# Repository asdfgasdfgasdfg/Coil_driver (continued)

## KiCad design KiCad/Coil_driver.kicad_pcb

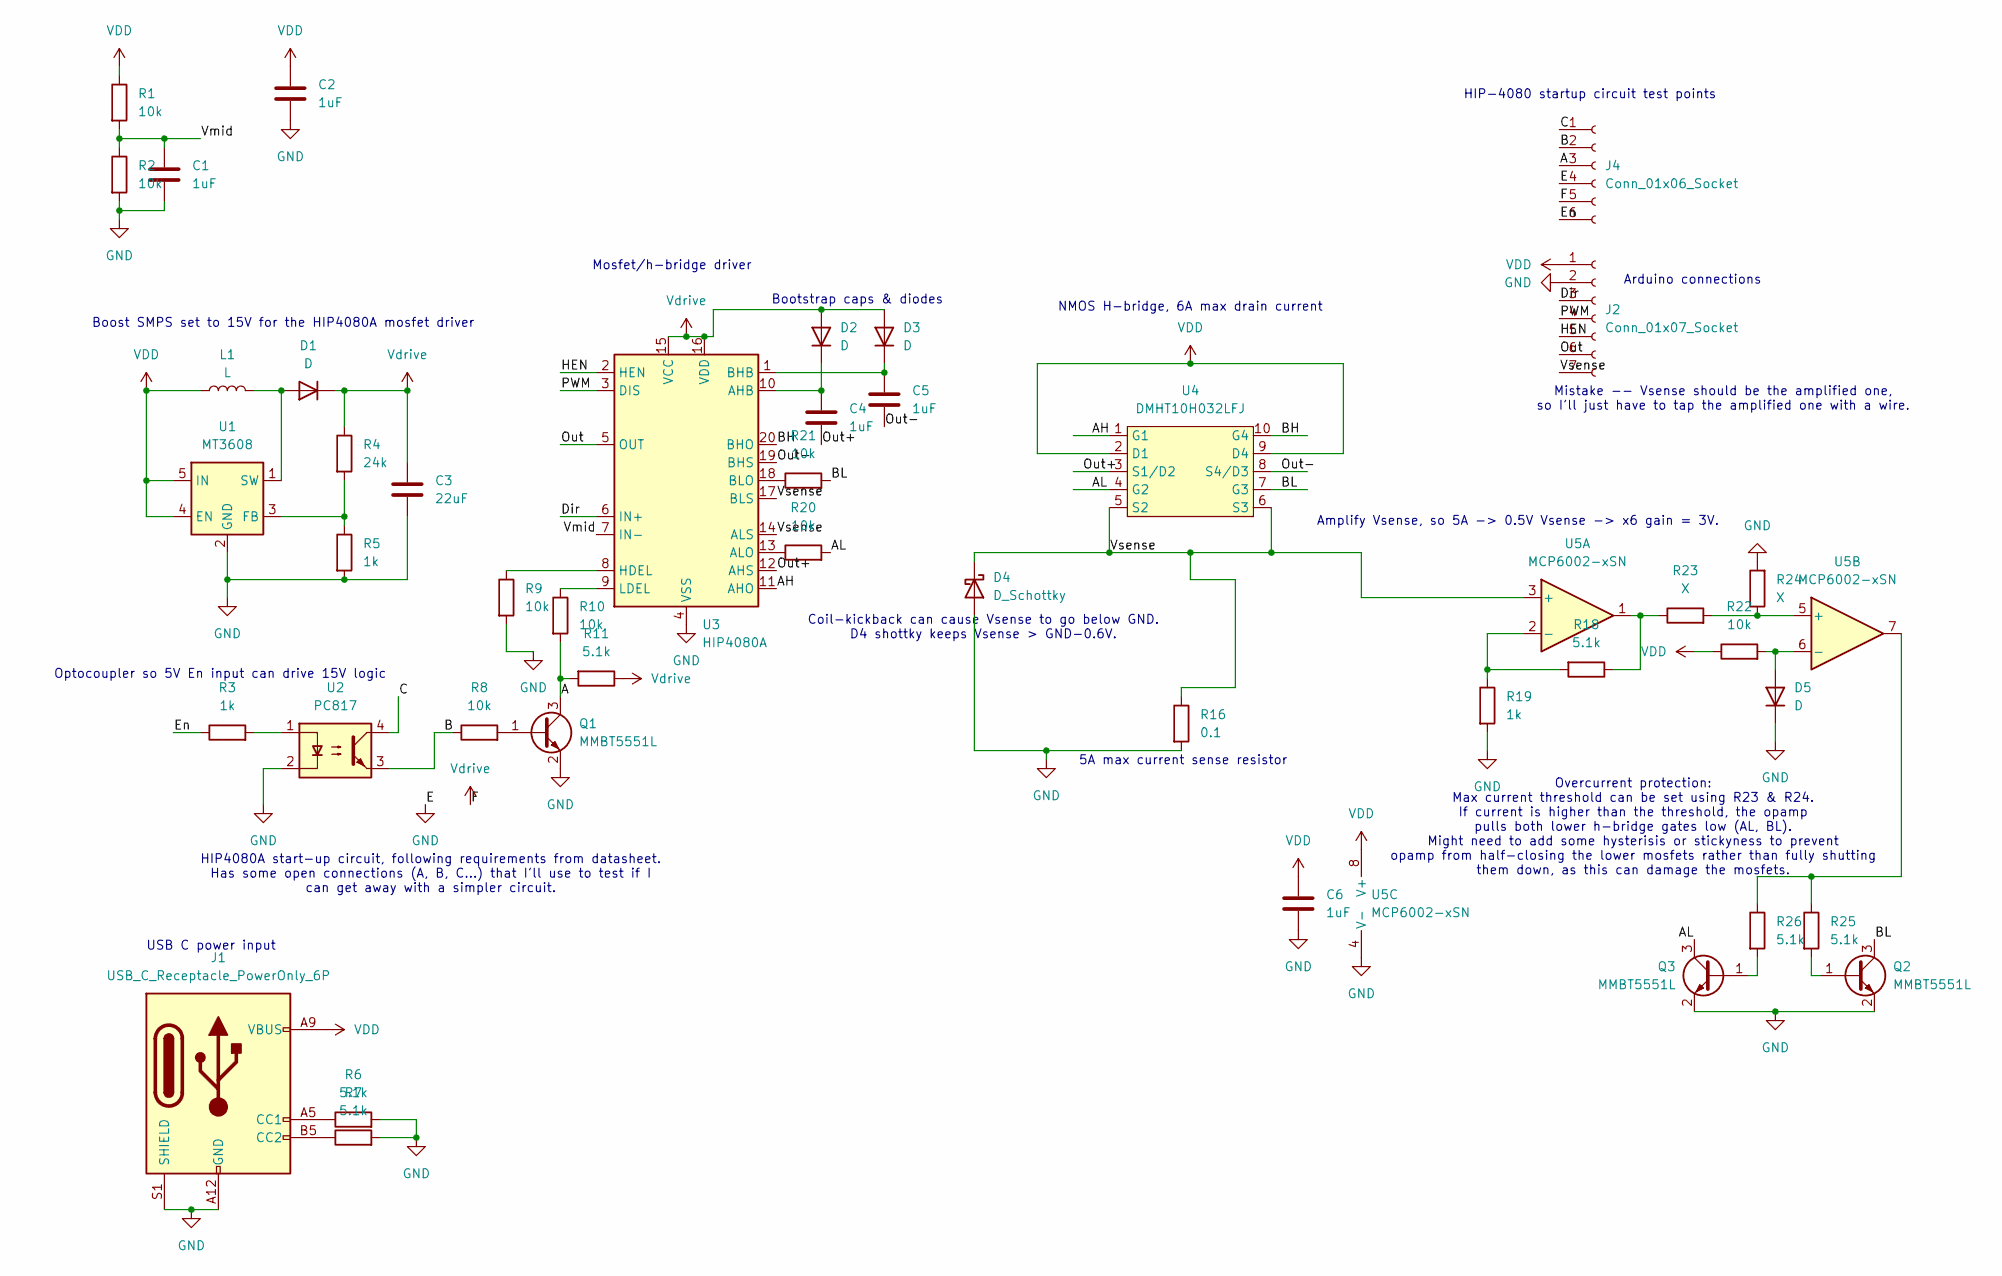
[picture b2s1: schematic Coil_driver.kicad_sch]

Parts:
C1, C2, C4, C5, C6: 1uF; C_0603_1608Metric
C3: 22uF; C_1206_3216Metric
D1, D2, D3, D5: D; D_SOD-123
D4: D_Schottky; D_SMA
J1: USB_C_Receptacle_PowerOnly_6P; USB_C_Receptacle_GCT_USB4135-GF-A_6P_TopMnt_Horizontal; LCSC C2927028
J2: Conn_01x07_Socket; PinSocket_1x07_P2.54mm_Vertical
J4: Conn_01x06_Socket; PinSocket_1x06_P2.54mm_Vertical
L1: L; L_Axial_L5.3mm_D2.2mm_P2.54mm_Vertical_Vishay_IM-1
Q1, Q2, Q3: MMBT5551L; SOT-23
R1, R2, R8, R9, R10, R20, R21, R22: 10k; R_0603_1608Metric
R3, R5, R19: 1k; R_0603_1608Metric
R4: 24k; R_0603_1608Metric
R6, R7: 5.1k; R_0603_1608Metric; LCSC C23186
R11, R18, R25, R26: 5.1k; R_0603_1608Metric
R16: 0.1; R_1206_3216Metric
R23, R24: X; R_Axial_DIN0204_L3.6mm_D1.6mm_P1.90mm_Vertical
U1: MT3608; SOT-23-6
U2: PC817; DIP-4_W7.62mm
U3: HIP4080A; SOIC-20W_7.5x12.8mm_P1.27mm
U4: DMHT10H032LFJ; V-DFN5045-12
U5: MCP6002-xSN; SOIC-8_3.9x4.9mm_P1.27mm

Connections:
/A: J4.3, Q1.3 (C), R10.2, R11.2
/AH: U3.11 (AHO), U4.1 (G1)
/AL: Q3.3 (C), R20.2, U4.4 (G2)
/B: J4.2, R8.1, U2.3
/BH: U3.20 (BHO), U4.10 (G4)
/BL: Q2.3 (C), R21.2, U4.7 (G3)
/C: J4.1, U2.4
/Dir: J2.3, U3.6 (IN+); also elsewhere on the board
/En: J4.6, R3.1; also elsewhere on the board
/HEN: J2.5, U3.2 (HEN); also elsewhere on the board
/Out: J2.6, U3.5 (OUT); also elsewhere on the board
/Out+: C4.2, U3.12 (AHS), U4.3 (S1/D2)
/Out-: C5.2, U3.19 (BHS), U4.8 (S4/D3)
/PWM: J2.4, U3.3 (DIS); also elsewhere on the board
/Vmid: C1.1, R1.2, R2.1, U3.7 (IN-)
/Vsense: D4.1 (K), J2.7, R16.1, U3.14 (ALS), U3.17 (BLS), U4.5 (S2), U4.6 (S3), U5.3 (+); also elsewhere on the board
GND: C1.2, C2.2, C3.2, C6.2, D4.2 (A), D5.1 (K), J1.A12 (GND), J1.B12 (GND), J1.S1 (SHIELD), J2.2, J4.4, Q1.2 (E), Q2.2 (E), Q3.2 (E), R2.2, R5.2, R6.2, R7.2, R9.2, R16.2, R19.2, R24.2, U1.2 (GND), U2.2, U3.4 (VSS), U5.4 (V-); also elsewhere on the board
unnamed: D1.2 (A), L1.2, U1.1 (SW)
unnamed: C4.1, D2.1 (K), U3.10 (AHB)
unnamed: C5.1, D3.1 (K), U3.1 (BHB)
unnamed: D5.2 (A), R22.2, U5.6 (-)
unnamed: J1.A5 (CC1), R6.1
unnamed: J1.B5 (CC2), R7.1
unnamed: Q1.1 (B), R8.2
unnamed: Q2.1 (B), R25.2
unnamed: Q3.1 (B), R26.2
unnamed: R3.2, U2.1
unnamed: R18.1, R23.1, U5.1
unnamed: R25.1, R26.1, U5.7
unnamed: R4.2, R5.1, U1.3 (FB)
unnamed: R20.1, U3.13 (ALO)
unnamed: R21.1, U3.18 (BLO)
unnamed: R9.1, U3.8 (HDEL)
unnamed: R10.1, U3.9 (LDEL)
unnamed: R18.2, R19.1, U5.2 (-)
unnamed: R23.2, R24.1, U5.5 (+)
VDD: C2.1, C6.1, J1.A9 (VBUS), J1.B9 (VBUS), J2.1, L1.1, R1.1, R22.1, U1.4 (EN), U1.5 (IN), U4.2 (D1), U4.9 (D4), U5.8 (V+); also elsewhere on the board
Vdrive: C3.1, D1.1 (K), D2.2 (A), D3.2 (A), J4.5, R4.1, R11.1, U3.15 (VCC), U3.16 (VDD)

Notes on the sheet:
Bootstrap caps & diodes
Arduino connections
Boost SMPS set to 15V for the HIP4080A mosfet driver
Mosfet/h-bridge driver
5A max current sense resistor
HIP4080A start-up circuit, following requirements from datasheet. Has some open connections (A, B, C...) that I'll use to test if I can get away with a simpler circuit.
NMOS H-bridge, 6A max drain current
USB C power input
Overcurrent protection: Max current threshold can be set using R23 & R24. If current is higher than the threshold, the opamp pulls both lower h-bridge gates low (AL, BL). Might need to add some hysterisis or stickyness to prevent opamp from half-closing the lower mosfets rather than fully shutting 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
Optocoupler so 5V En input can drive 15V logic
Coil-kickback can cause Vsense to go below GND. D4 shottky keeps Vsense > GND-0.6V.
Mistake -- Vsense should be the amplified one, so I'll just have to tap the amplified one with a wire.
Amplify Vsense, so 5A -> 0.5V Vsense -> x6 gain = 3V.
HIP-4080 startup circuit test points

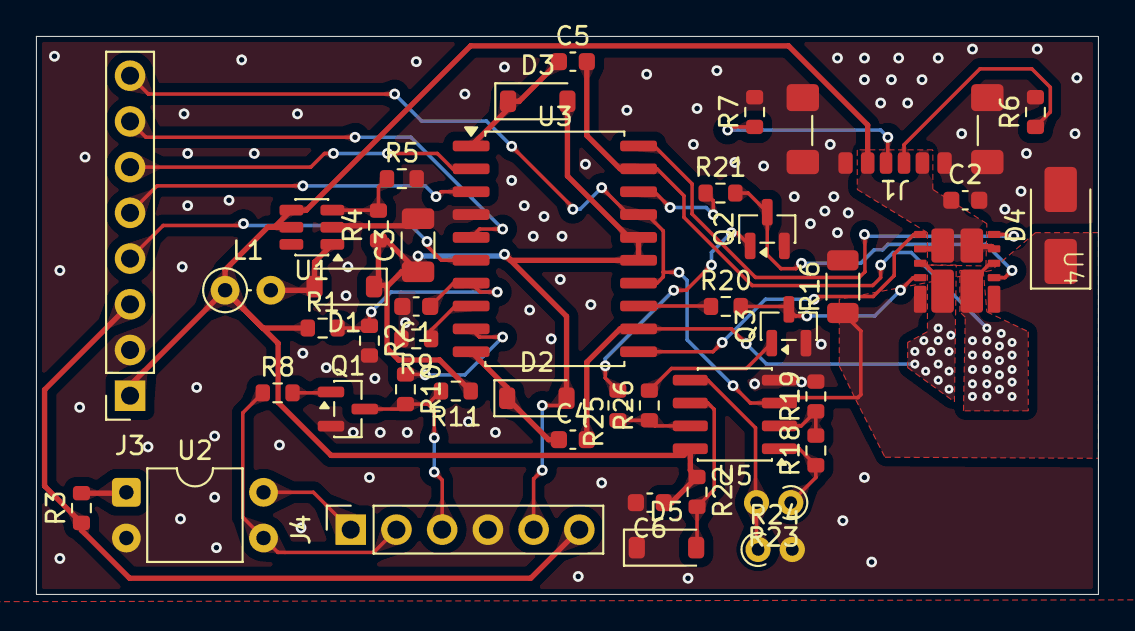
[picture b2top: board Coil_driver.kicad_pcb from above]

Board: 2 copper layers, 59.0 x 31.0 mm, 44 parts (0 on the bottom side), 38 nets.

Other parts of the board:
J3: Conn_01x08_Socket; PinSocket_1x08_P2.54mm_Vertical

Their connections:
/Dir: J3.4; also elsewhere on the board
/En: J3.3; also elsewhere on the board
/HEN: J3.6; also elsewhere on the board
/Out: J3.7; also elsewhere on the board
/PWM: J3.5; also elsewhere on the board
/Vsense: J3.8; also elsewhere on the board
GND: J3.2; also elsewhere on the board
VDD: J3.1; also elsewhere on the board

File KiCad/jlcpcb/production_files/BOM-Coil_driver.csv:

Comment,Designator,Footprint,LCSC,Quantity
0.1,R16,R_1206_3216Metric,C42460614,1
10k,"R1,R10,R2,R20,R21,R22,R8,R9",R_0603_1608Metric,C25804,8
1k,"R19,R3,R5",R_0603_1608Metric,C21190,3
1uF,"C1,C2,C4,C5,C6",C_0603_1608Metric,C15849,5
22uF,C3,C_1206_3216Metric,C12891,1
24k,R4,R_0603_1608Metric,C23352,1
5.1k,"R11,R18,R25,R26,R6,R7",R_0603_1608Metric,C23186,6
D,"D1,D2,D3,D5",D_SOD-123,C8598,4
D_Schottky,D4,D_SMA,C22452,1
HIP4080A,U3,SOIC-20W_7.5x12.8mm_P1.27mm,C3655064,1
MCP6002-xSN,U5,SOIC-8_3.9x4.9mm_P1.27mm,C7377,1
MMBT5551L,"Q1,Q2,Q3",SOT-23,C2145,3
MT3608,U1,SOT-23-6,C84817,1
USB_C_Receptacle_PowerOnly_6P,J1,USB_C_Receptacle_GCT_USB4135-GF-A_6P_TopMnt_Horizontal,C2927028,1

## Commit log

2026-04-22 Added media for cv and stuff
2026-04-26 Version 1 checkpoint
2026-05-27 schematic v1
    lcsc, component values, and footprints not finalised. shit is too big rn.
2026-05-30 schematic FINAL! (I hope)
2026-05-30 PCB Almost done with one coil!!
2026-05-31 saving here before i try making PerCoilFlipped on schematic
2026-05-31 Fixed schematic after annotation fuck up
2026-05-31 PCB - Right side coil done
2026-05-31 Added LEDs to schematic & PCB
2026-05-31 sch - Added label to unnamed net LminToRsense
2026-05-31 PCB
    Gate connections done.
    All power except 5V done (Vbus, Vdrive).
    Power path done, with minor tweaks needed (OC_sense right wider, GND plane on left kinda blocked off)
2026-06-01 Big changes to power path & current sense (PerCoil)
    Found out how to do this symmetrically. Should've done this to begin with.
    A/B will be the same sides for both h-bridges.
    Lmin, Rsense, etc have to be swapped around from AHS to BHS on opposite coils.
    INA diff amp has to be hooked up to Rsense in different directions to maintain AH->BL = positive current direction.
    Also, now that I'm confident which way is positive etc, I'm going to remove the SPDT solder bridge and just commit to it.
2026-06-01 Made changes to schematic and just updated PCB from schematic. Haven't edited PCB yet.
2026-06-01 PCB edits
    Power path fixed. INA diff amp fixed.
    HIP<->H-bridge connections removed, will be redone.
    SPDT solder bridge removed, will be redone.
2026-06-01 Top power path basically finalised
    Finished HIP<->Hbridge done
2026-06-01 minor bug
    whoops! Mixed up my Analog pins A1 & A2 with my state pins A1 & A2. That would've been bad 😅
2026-06-01 Gonna push before I revert PCB. PCB seems to have gotten fked at some point.
2026-06-01 DAC logic
    - Internal connections done
    - Spacing, shorts, nets, etc verified
    - Grouped
2026-06-01 USBC power & Boost SMPS done
    - Internal connections done
    - Spacing, shorts, nets, etc verified
    - Grouped
2026-06-01 Triangle wave done
    - Internal connections done
    - Spacing, shorts, nets, etc verified
    - Grouped
    *Doesn't fit now...
2026-06-01 HF PWM done for both coils
2026-06-01 Hoo man
    Right side coil type shit
2026-06-01 Bunchhh of shit
    PCB looking gooood
2026-06-01 Only GND via stitching left!!!
    OMG OMG OMG PLEASE NO HUGE ERRORS
2026-06-01 Final version before trying JLCPCB
2026-06-01 DONE AND DUSTED
    (God I hope it's gonna work...)
    (God it's not gonna work... 😭 )
    AHHHHHH
2026-06-04 goddammit forgot teardrops and final cleanup...
2026-06-10 Fixed AND Gate pins, added extra DAC logic Mux
    DAC logic mux not yet done on PCB
2026-06-29 V2 test code (coil_driver_v2), current sense results
2026-06-29 Added media mentioned in report
